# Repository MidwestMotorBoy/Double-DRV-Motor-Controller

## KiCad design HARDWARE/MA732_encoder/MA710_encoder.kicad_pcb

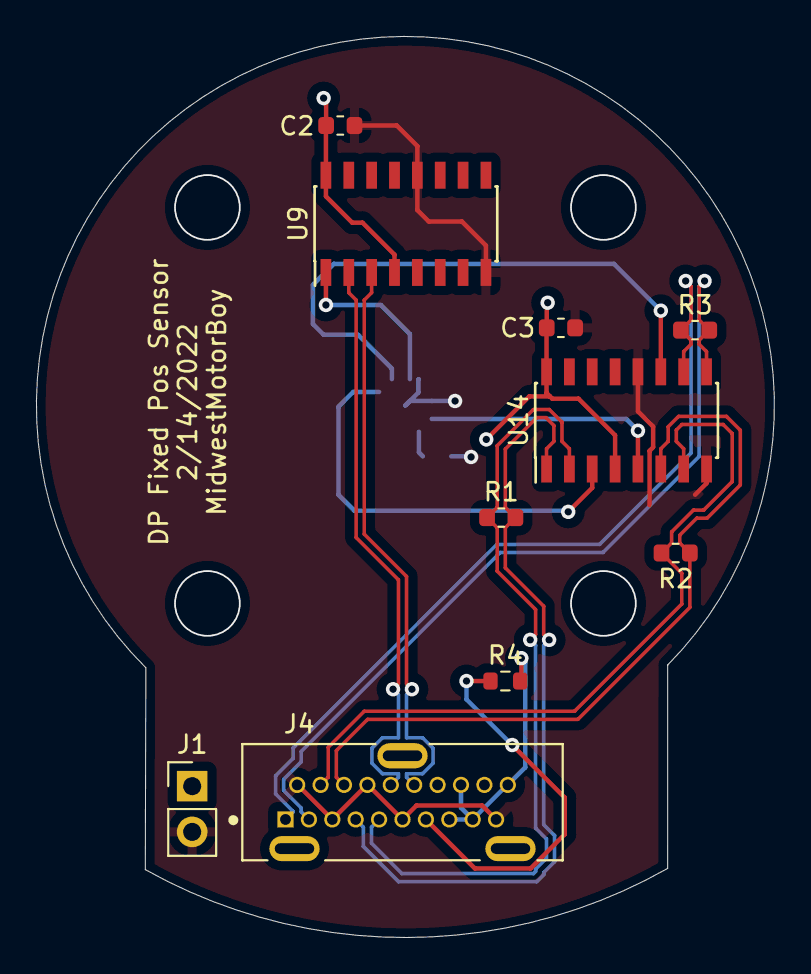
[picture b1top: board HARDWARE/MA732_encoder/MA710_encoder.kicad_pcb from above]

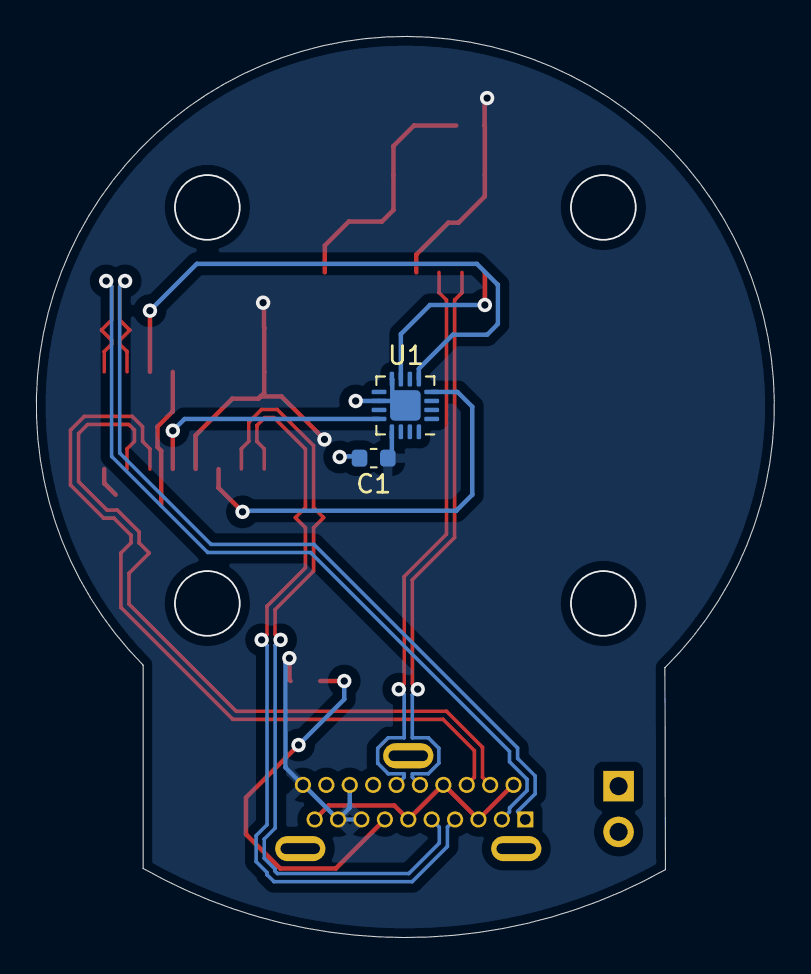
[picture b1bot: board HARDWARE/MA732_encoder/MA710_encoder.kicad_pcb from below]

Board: 2 copper layers, 41.0 x 50.1 mm, 12 parts (2 on the bottom side), 15 nets.

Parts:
C1, C2, C3: 1uF; C_0603_1608Metric
J1: Conn_01x02_Male; PinHeader_1x02_P2.54mm_Vertical
J4: 47272-0001; TE_2041441-1
R1, R2, R3: 100Ω; R_0603_1608Metric
R4: 0Ω; R_0603_1608Metric
U1: MA730; QFN-16-1EP_3x3mm_P0.5mm_EP1.7x1.7mm
U9: SN65LVDS31D; SOIC-16_3.9x9.9mm_P1.27mm
U14: SN65LVDS33D; SOIC-16_3.9x9.9mm_P1.27mm

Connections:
+3V3: C1.1, C2.1, C3.1, J4.15, J4.16, J4.17, J4.20, R4.2, U1.13 (VDD), U9.4 (G), U9.16 (VCC), U14.4 (G), U14.16 (VCC)
GND: C1.2, C2.2, C3.2, J1.2, J4.2, J4.5, J4.8, J4.11, J4.19, U1.8 (GND), U1.10 (TEST), U1.17 (PAD), U9.8 (GND), U9.12 (~G), U14.8 (GND), U14.12 (~G)
SPI6_MISO: U1.7 (MISO), U9.1 (1A)
SPI6_MISO_+: J4.12, U9.3 (1Z)
SPI6_MISO_-: J4.10, U9.2 (1Y)
SPI6_MOSI: U1.4 (MOSI), U14.3 (1Y)
SPI6_MOSI_+: J4.9, R1.1, U14.2 (1A)
SPI6_MOSI_-: J4.7, R1.2, U14.1 (1B)
SPI6_SCK: U1.12 (SCLK), U14.5 (2Y)
SPI6_SCK_+: J4.6, R2.1, U14.6 (2A)
SPI6_SCK_-: J4.4, R2.2, U14.7 (2B)
SPI6_nSS: U1.5 (~CS), U14.11 (3Y)
SPI6_nSS_+: J4.3, R3.1, U14.9 (3B)
SPI6_nSS_-: J4.1, R3.2, U14.10 (3A)
TEMP_1: J1.1, J4.13, R4.1

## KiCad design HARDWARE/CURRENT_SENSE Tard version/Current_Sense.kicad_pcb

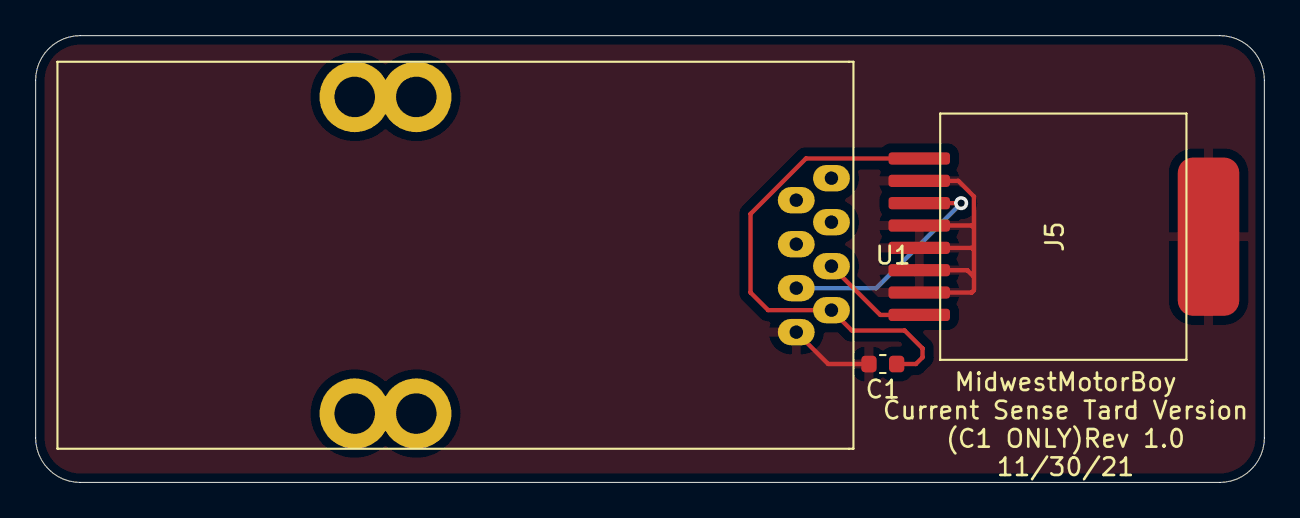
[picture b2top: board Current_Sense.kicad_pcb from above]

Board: 2 copper layers, 69.8 x 25.4 mm, 3 parts (0 on the bottom side), 4 nets.

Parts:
C1: 1uF; C_0603_1608Metric
J5: Conn_01x08; RCH-RC02015
U1: HO-150-PW-0000

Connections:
+5V: C1.1, J5.8, U1.7 (Vc)
DFSDM1_CKIN5_5V: J5.1, U1.5 (CLK)
DFSDM1_DATIN5_5V: J5.6, U1.6 (Dout)
GND: C1.2, J5.2, J5.3, J5.4, J5.5, J5.7, J5.9, U1.2 (GND), U1.8 (GND)

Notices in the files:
Core/Src/stm32h7xx_hal_msp.c:
© Copyright (c) 2021 STMicroelectronics.
All rights reserved.
This software component is licensed by ST under BSD 3-Clause license,
the "License"; You may not use this file except in compliance with the
License. You may obtain a copy of the License at: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
